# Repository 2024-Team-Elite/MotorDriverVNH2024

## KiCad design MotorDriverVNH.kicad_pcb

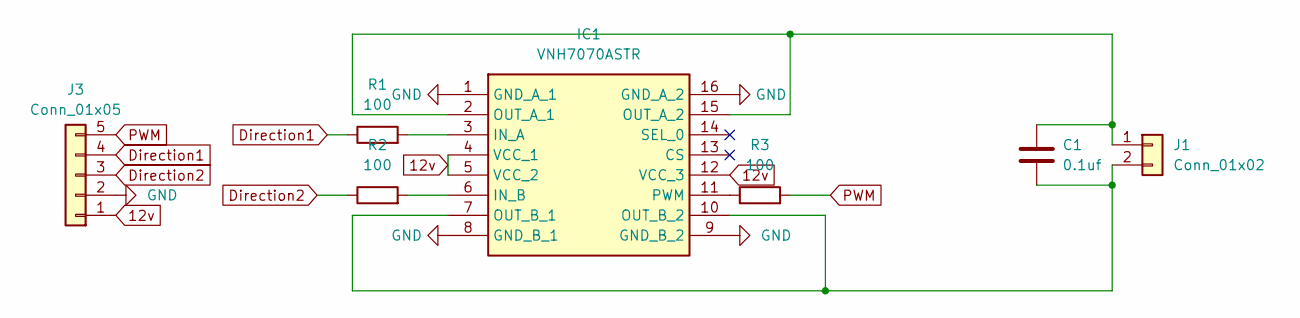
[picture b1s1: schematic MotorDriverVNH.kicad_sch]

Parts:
C1: 0.1uf; C_0805_2012Metric_Pad1.18x1.45mm_HandSolder
IC1: VNH7070ASTR; SOIC127P600X175-16N; Mouser Part Number 511-VNH7070ASTR
J1: Conn_01x02; PinHeader_1x02_P2.54mm_Vertical
J3: Conn_01x05; PinHeader_1x05_P2.54mm_Vertical
R1, R2, R3: 100; R_0805_2012Metric_Pad1.20x1.40mm_HandSolder

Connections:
12v: IC1.4 (VCC_1), IC1.5 (VCC_2), IC1.12 (VCC_3), J3.1
Direction1: J3.4, R1.1
Direction2: J3.3, R2.1
GND: IC1.1 (GND_A_1), IC1.8 (GND_B_1), IC1.9 (GND_B_2), IC1.16 (GND_A_2), J3.2
unnamed: IC1.3 (IN_A), R1.2
unnamed: IC1.6 (IN_B), R2.2
unnamed: C1.1, IC1.2 (OUT_A_1), IC1.15 (OUT_A_2), J1.1
unnamed: C1.2, IC1.7 (OUT_B_1), IC1.10 (OUT_B_2), J1.2
unnamed: IC1.11 (PWM), R3.1
PWM: J3.5, R3.2

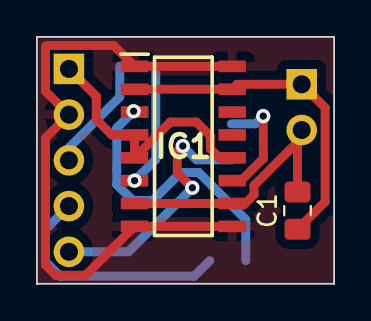
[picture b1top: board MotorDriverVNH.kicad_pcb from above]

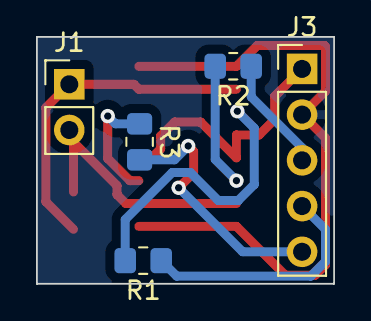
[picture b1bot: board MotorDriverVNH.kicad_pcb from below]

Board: 2 copper layers, 16.5 x 13.7 mm, 7 parts (5 on the bottom side), 10 nets.

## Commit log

2024-03-08 Added Resistors
2024-03-10 Routed Resistors
2024-03-10 Finished
2024-04-14 Cleaning
